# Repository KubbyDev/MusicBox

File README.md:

# MusicBox

A Music box with only dumb/homemade instruments. Currently I plan on making 5 instruments. All these instruments will be played automatically by the music box from preprocessed files.

### Stepper motors

First prototype done  

### Drum

Prototype code is ready to be tested

### Slide Whistle

Some simple prototypes were made but without sufficient performances for the moment.

### Tesla tower

Nothing for the moment

### Laser harp

First prototype in progress

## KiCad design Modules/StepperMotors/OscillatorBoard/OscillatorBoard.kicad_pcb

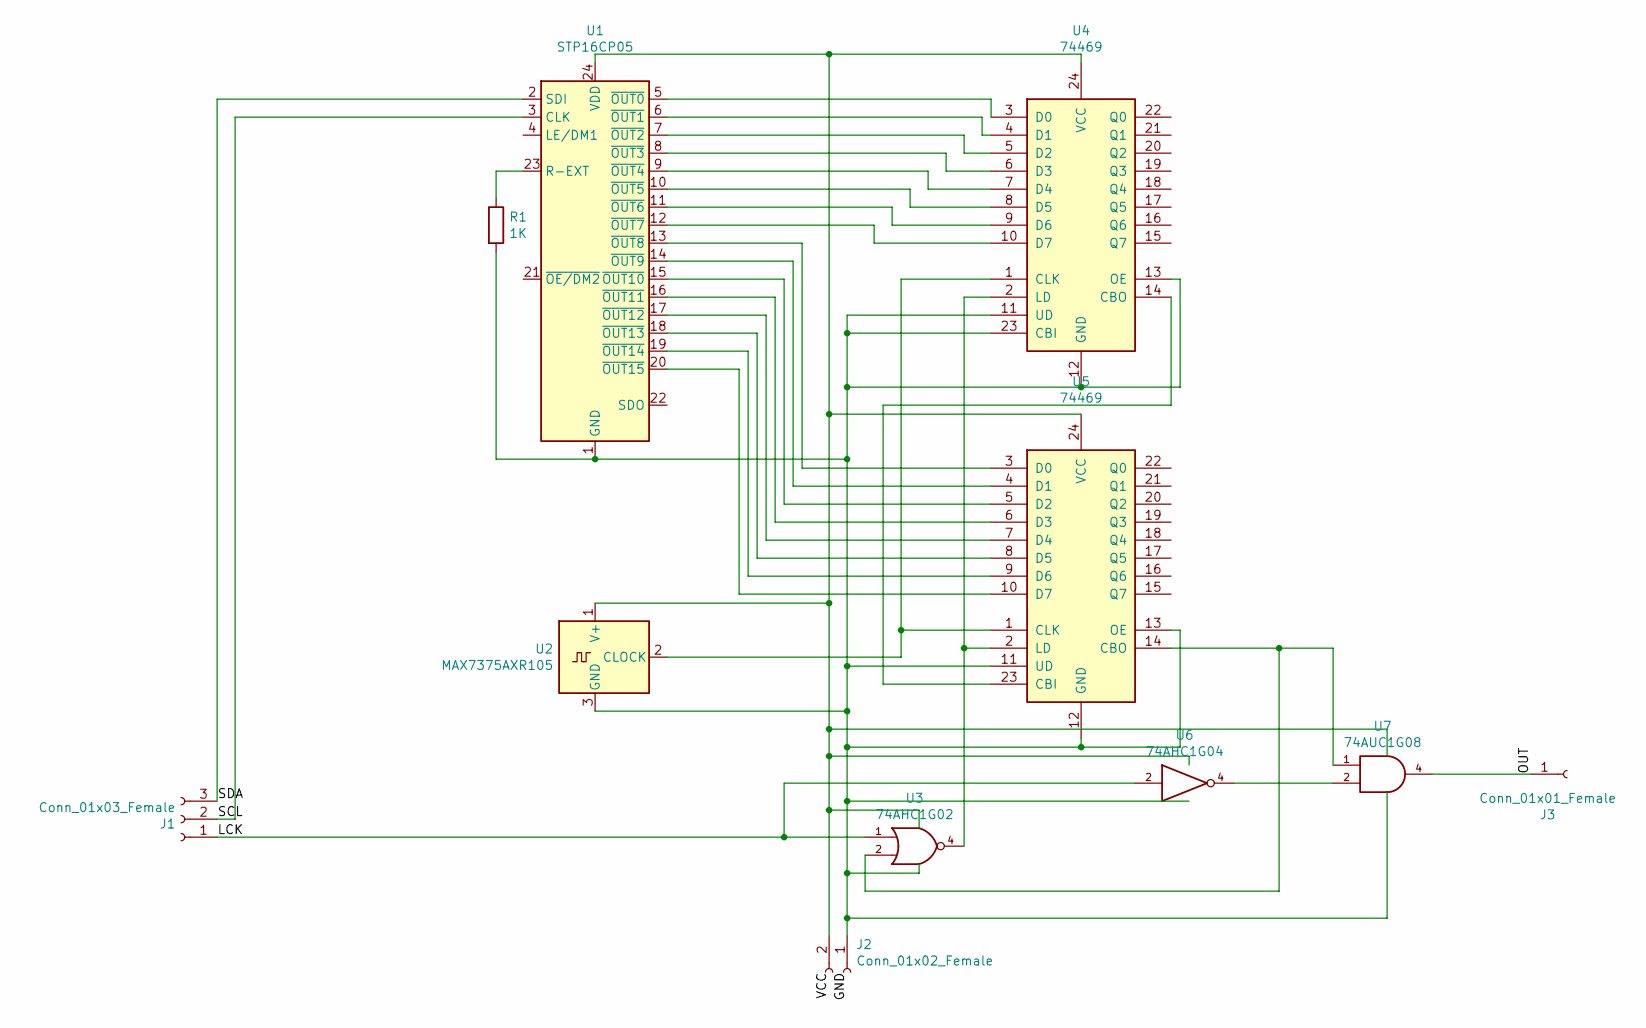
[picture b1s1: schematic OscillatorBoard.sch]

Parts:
J1: Conn_01x03_Female; PinSocket_1x03_P2.00mm_Vertical
J2: Conn_01x02_Female; PinSocket_1x02_P2.00mm_Vertical
J3: Conn_01x01_Female; PinSocket_1x01_P2.00mm_Vertical
R1: 1K; R_Axial_DIN0204_L3.6mm_D1.6mm_P5.08mm_Horizontal
U1: STP16CP05; QSOP-24_3.9x8.7mm_P0.635mm
U2: MAX7375AXR105; SOT-323_SC-70
U3: 74AHC1G02; SOT-23-5
U4, U5: 74469; DIP-24_W7.62mm
U6: 74AHC1G04; SOT-143
U7: 74AUC1G08; SOT-23-5

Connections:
/LCK: J1.1, U3.1, U6.2
/OUT: J3.1, U7.4
/SCL: J1.2, U1.3 (CLK)
/SDA: J1.3, U1.2 (SDI)
GND: J2.1, R1.2, U1.1 (GND), U2.3 (GND), U3.3 (GND), U4.11 (UD), U4.12 (GND), U4.13 (OE), U4.23 (CBI), U5.11 (UD), U5.12 (GND), U5.13 (OE), U6.3 (GND), U7.3 (GND)
unnamed: R1.1, U1.23 (R-EXT)
unnamed: U1.5 (~OUT0), U4.3 (D0)
unnamed: U1.6 (~OUT1), U4.4 (D1)
unnamed: U1.7 (~OUT2), U4.5 (D2)
unnamed: U1.8 (~OUT3), U4.6 (D3)
unnamed: U1.9 (~OUT4), U4.7 (D4)
unnamed: U1.10 (~OUT5), U4.8 (D5)
unnamed: U1.11 (~OUT6), U4.9 (D6)
unnamed: U1.12 (~OUT7), U4.10 (D7)
unnamed: U1.13 (~OUT8), U5.3 (D0)
unnamed: U1.14 (~OUT9), U5.4 (D1)
unnamed: U1.15 (~OUT10), U5.5 (D2)
unnamed: U1.16 (~OUT11), U5.6 (D3)
unnamed: U1.17 (~OUT12), U5.7 (D4)
unnamed: U1.18 (~OUT13), U5.8 (D5)
unnamed: U1.19 (~OUT14), U5.9 (D6)
unnamed: U1.20 (~OUT15), U5.10 (D7)
unnamed: U2.2 (CLOCK), U4.1 (CLK), U5.1 (CLK)
unnamed: U3.2, U5.14 (CBO), U7.1
unnamed: U3.4, U4.2 (LD), U5.2 (LD)
unnamed: U4.14 (CBO), U5.23 (CBI)
unnamed: U6.4, U7.2
VCC: J2.2, U1.24 (VDD), U2.1 (V+), U3.5 (VCC), U4.24 (VCC), U5.24 (VCC), U6.5 (VCC), U7.5 (VCC)

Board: 2 copper layers, 11 parts (0 on the bottom side), 28 nets, no tracks yet.

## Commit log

2020-05-16 First tests with stepper
2020-05-24 Found some ideas and resources
2020-05-26 Drum and OldStepper tests
2020-06-01 Air Blower model
2020-06-02 SlideWhistle body v1 almost done
2020-06-05 SlideWhistle v1
2020-06-12 Slide Whistle fix
2020-06-12 Tests
2020-06-16 First stepper music
2020-06-16 Slide whistle tests
2020-06-23 StepperMotors module base done
2020-06-25 Better code for steppers (TO TEST)
2020-06-25 Removed big and useless images
2020-06-25 Power Supply researches
2020-06-30 Stepper motors module done
2020-06-30 Started MIDI to Notes/Durations converter
2020-07-01 Steppers module v1
2020-07-02 Slide whistle design V2
2020-07-05 Slide Whistle V2 results + Servo testing
2020-07-08 MidiToUsable tests
2020-07-11 Started making the Control Panel with React app
2020-07-11 MelodyProcessing algorithms
2020-07-11 Basic partitions rendering
2020-07-13 MelodyProcessing base done
2020-07-14 ControlPanel webapp: Instrument selection
2020-07-14 ControlPanel webapp: Improved the instrument selection dropdown
2020-07-15 MidiToNotes done
2020-07-17 NotesToInstrument structure
2020-07-17 OscillatorBoard draft
2020-07-17 ControlPanel Browser MelodyPlayer
2020-07-18 Basic (very basic lol) home page
2020-07-18 Python server with flask to serve web app
2020-07-20 Server-Interface link for MidiToNotes
2020-07-20 Server-Interface link for NotesToInstrument's requirements part
2020-07-21 Small webapp improvements
2020-07-21 Octave number correction
2020-07-21 OscillatorBoard Concept2 + First kicad schematic
2020-07-22 Simple drum Arduino code
2020-07-23 Errors display on partition
2020-07-25 ControlPanel server: JobManager
2020-07-25 Started track preprocess interface
2020-07-25 Server programs reorganization + tracks processing backend
2020-07-26 KiCAD tests (Oscillator Board)
2020-07-27 Server reorganization
2020-08-01 Melody generation backend
2020-08-01 Laser diode test
2020-08-01 Oops
2020-08-01 Backend improvements + Frontend generation button
2020-08-02 Progress functions + Fixes
2020-08-03 Steppers visual idea
2020-08-05 Fixes + Melodies list
2020-08-06 Melody name selector + Fixes
2020-08-14 LaserHarp: Notes synthesizing
2020-08-23 LaserHarp code to be tested
2020-09-05 Harp generation code
2020-09-07 LaserHarp more or less working (not autoplaying)
2020-12-25 Laser holder and arduino fixes
2021-07-20 Bump react-native from 0.63.0 to 0.64.1 in /ControlPanel/webapp
    Bumps [react-native](https://github.com/facebook/react-native) from 0.63.0 to 0.64.1.
    - [Release notes](https://github.com/facebook/react-native/releases)
    - [Changelog](https://github.com/facebook/react-native/blob/main/Releases.md)
    - [Commits](https://github.com/facebook/react-native/compare/v0.63.0...v0.64.1)
    ---
    updated-dependencies:
2022-09-23 Move todolist here
2025-06-24 Bump pbkdf2 from 3.1.1 to 3.1.3 in /ControlPanel/webapp
    Bumps [pbkdf2](https://github.com/crypto-browserify/pbkdf2) from 3.1.1 to 3.1.3.
    - [Changelog](https://github.com/browserify/pbkdf2/blob/master/CHANGELOG.md)
    - [Commits](https://github.com/crypto-browserify/pbkdf2/compare/v3.1.1...v3.1.3)
    ---
    updated-dependencies:
    - dependency-name: pbkdf2
